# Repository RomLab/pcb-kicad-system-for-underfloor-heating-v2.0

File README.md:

# PCB for underfloor heating system v2.0

There are here schematics, PCBs, 3D views and Gerber data for devices in underfloor heating system. There are two types folders with version KiCAD 5 and KiCAD 7. The libraries are [here](https://github.com/RomLab/kicad-library).

More information at https://github.com/RomLab/system-for-underfloor-heating-v2.0

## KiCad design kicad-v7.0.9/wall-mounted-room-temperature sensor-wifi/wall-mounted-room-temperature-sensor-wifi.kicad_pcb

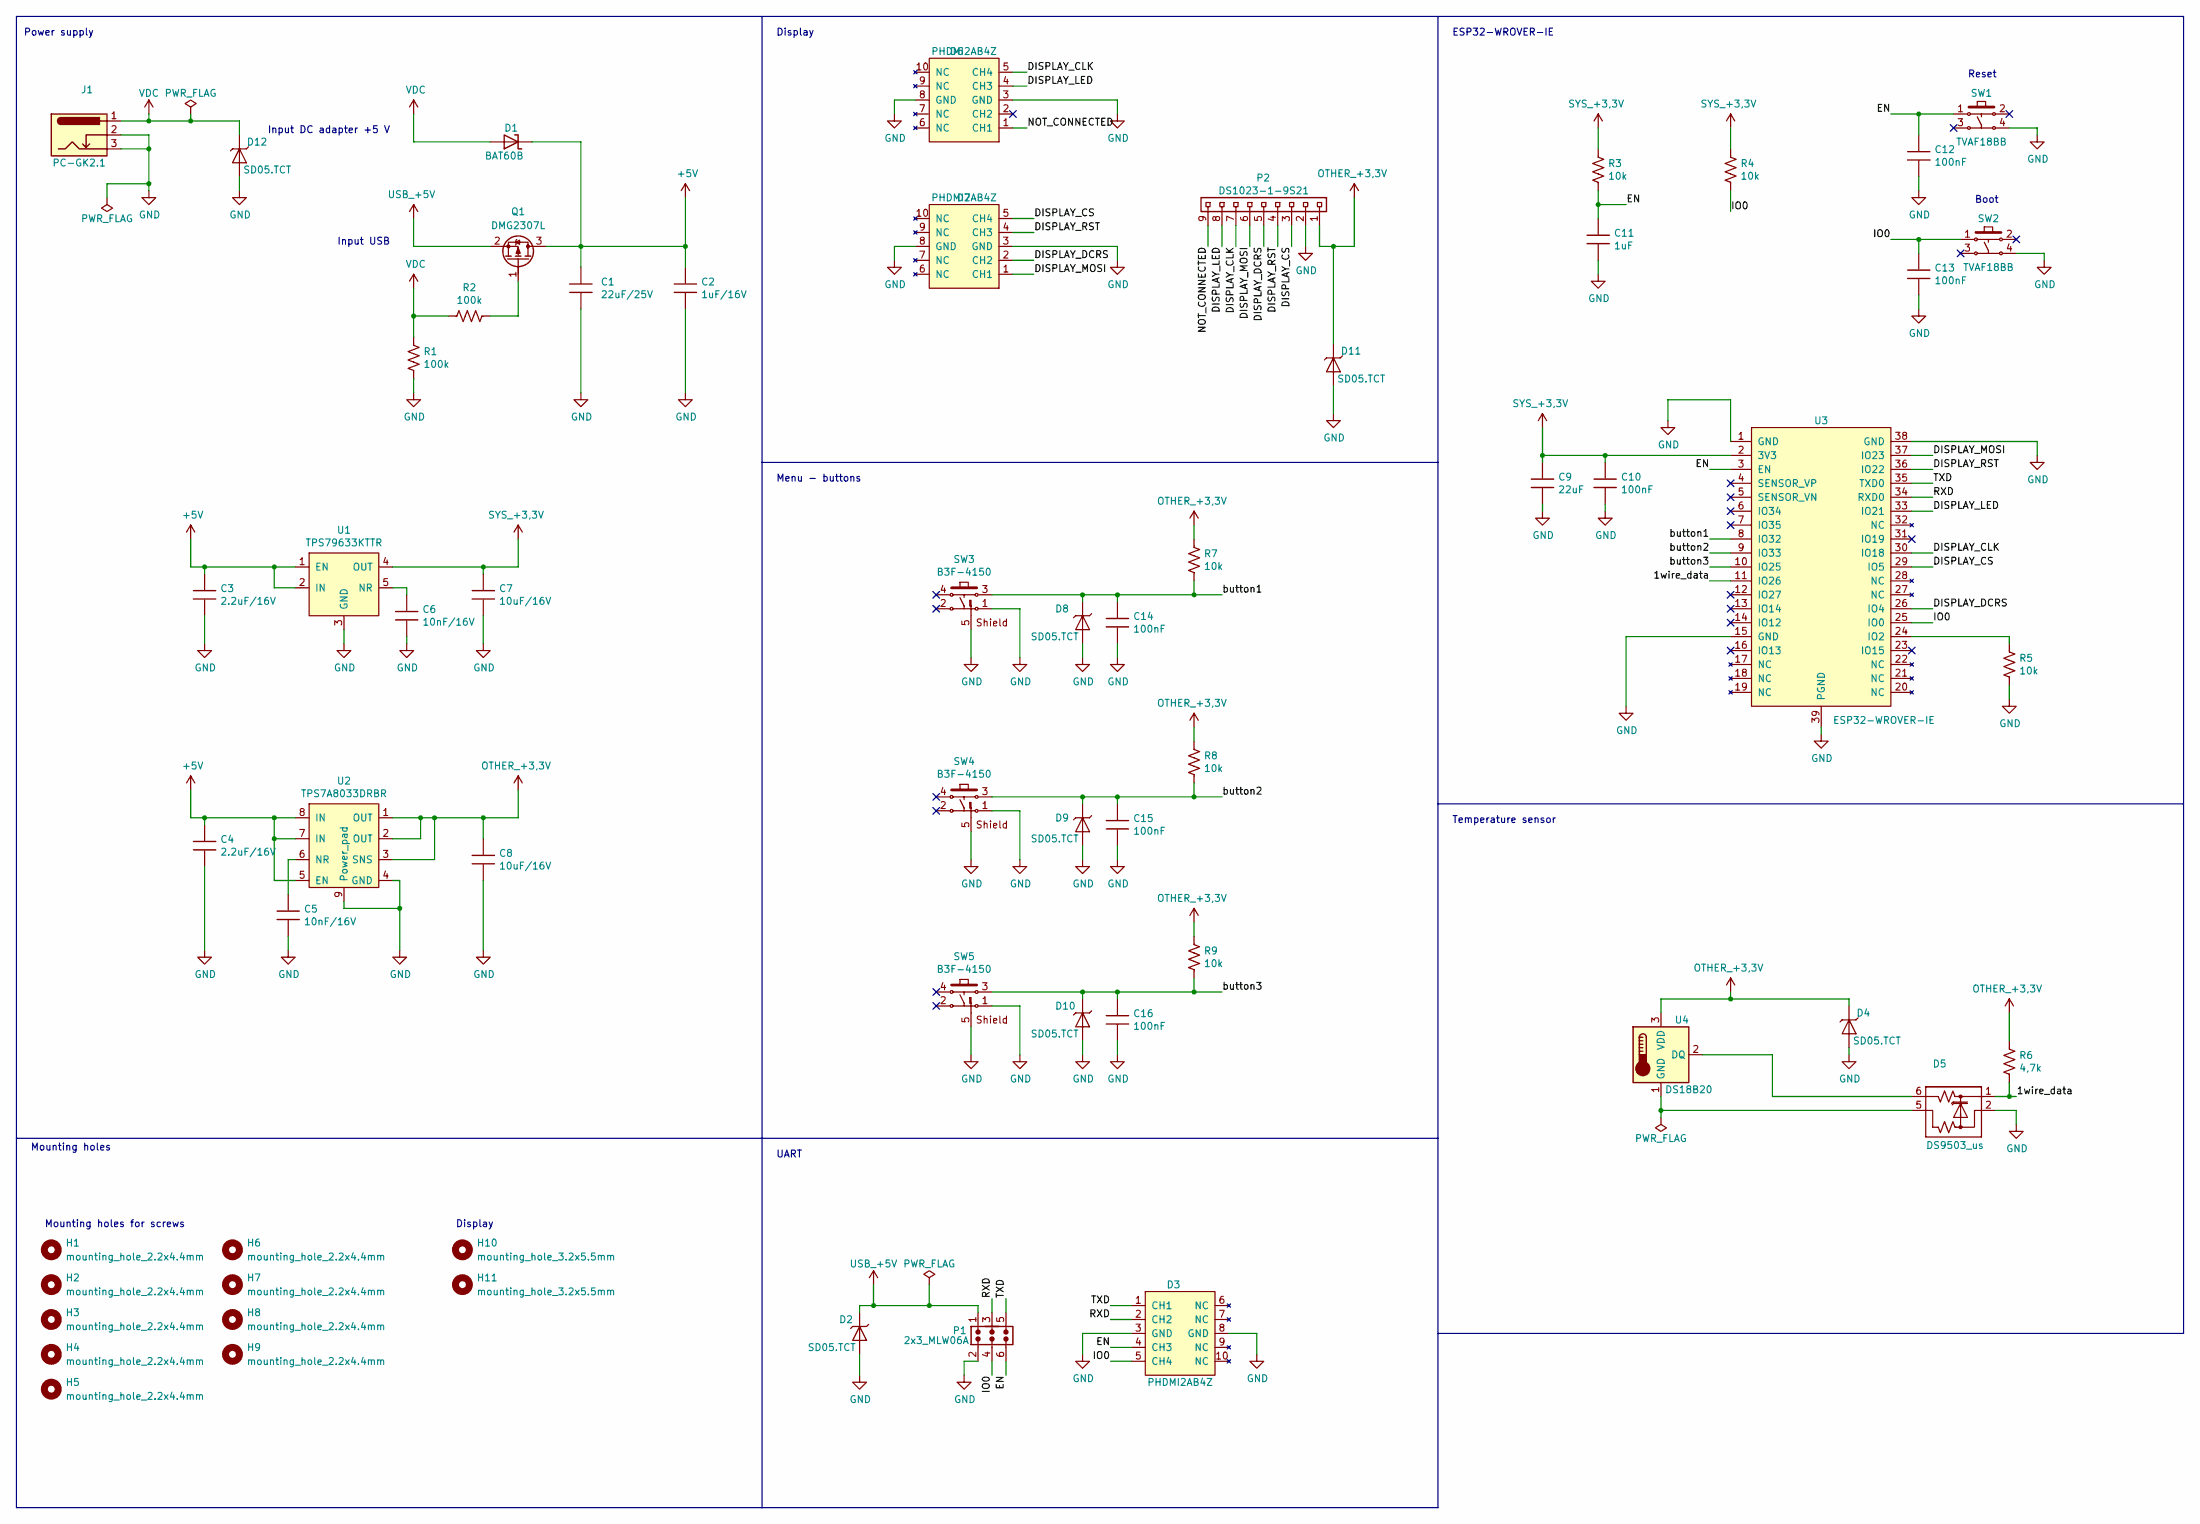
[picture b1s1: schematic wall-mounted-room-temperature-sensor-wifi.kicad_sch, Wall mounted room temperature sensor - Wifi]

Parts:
C1: 22uF/25V; c_0805
C2: 1uF/16V; c_0805
C3, C4: 2.2uF/16V; c_0805
C5, C6: 10nF/16V; c_0805
C7, C8: 10uF/16V; c_0805
C9: 22uF; c_0805
C10, C12, C13, C14, C15, C16: 100nF; c_0805
C11: 1uF; c_0805
D1: BAT60B; sod_323
D2, D4, D8, D9, D10, D11, D12: SD05.TCT; sod_323
D3, D6, D7: PHDMI2AB4Z; dfn_2510a_10
D5: DS9503_us; tsoc_6
H1, H2, H3, H4, H5, H6, H7, H8, H9: mounting_hole_2.2x4.4mm
H10, H11: mounting_hole_3.2x5.5mm
J1: PC-GK2.1
P1: 2x3_MLW06A
P2: DS1023-1-9S21; 1x9_pin_socket_2.54mm_vertical_8.5mm
Q1: DMG2307L; sot_23_3
R1, R2: 100k; r_0805
R3, R4, R5, R7, R8, R9: 10k; r_0805
R6: 4,7k; r_0805
SW1, SW2: TVAF18BB
SW3, SW4, SW5: B3F-4150
U1: TPS79633KTTR; to_263_5
U2: TPS7A8033DRBR; son_8
U3: ESP32-WROVER-IE
U4: DS18B20; to_92_in_line

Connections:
+5V: C1.1, C2.1, C3.1, C4.1, D1.1 (K), Q1.3 (D), U1.1 (EN), U1.2 (IN), U2.5 (EN), U2.7 (IN), U2.8 (IN)
/1wire_data: D5.1 (K), R6.2, U3.11 (IO26)
/DISPLAY_CLK: D6.5 (CH4), P2.7, U3.30 (IO18)
/DISPLAY_CS: D7.5 (CH4), P2.3, U3.29 (IO5)
/DISPLAY_DCRS: D7.2 (CH2), P2.5, U3.26 (IO4)
/DISPLAY_LED: D6.4 (CH3), P2.8, U3.33 (IO21)
/DISPLAY_MOSI: D7.1 (CH1), P2.6, U3.37 (IO23)
/DISPLAY_RST: D7.4 (CH3), P2.4, U3.36 (IO22)
/EN: C11.1, C12.1, D3.4 (CH3), P1.6, R3.2, SW1.1, U3.3 (EN)
/IO0: C13.1, D3.5 (CH4), P1.4, R4.2, SW2.1, U3.25 (IO0)
/NOT_CONNECTED: D6.1 (CH1), P2.9
/RXD: D3.2 (CH2), P1.3, U3.34 (RXD0)
/TXD: D3.1 (CH1), P1.5, U3.35 (TXD0)
/button1: C14.1, D8.1 (K), R7.2, SW3.3, U3.8 (IO32)
/button2: C15.1, D9.1 (K), R8.2, SW4.3, U3.9 (IO33)
/button3: C16.1, D10.1 (K), R9.2, SW5.3, U3.10 (IO25)
GND: C1.2, C2.2, C3.2, C4.2, C5.2, C6.2, C7.2, C8.2, C9.2, C10.2, C11.2, C12.2, C13.2, C14.2, C15.2, C16.2, D2.2 (A), D3.3 (GND), D3.8 (GND), D4.2 (A), D5.2 (A), D6.3 (GND), D6.8 (GND), D7.3 (GND), D7.8 (GND), D8.2 (A), D9.2 (A), D10.2 (A), D11.2 (A), D12.2 (A), J1.2, J1.3, P1.2, P2.2, R1.2, R5.2, SW1.4, SW2.4, SW3.1, SW3.5 (GND), SW4.1, SW4.5 (GND), SW5.1, SW5.5 (GND), U1.3 (GND), U2.4 (GND), U2.9 (Power_pad), U3.1 (GND), U3.15 (GND), U3.38 (GND), U3.39 (PGND)
unnamed: Q1.1 (G), R2.2
unnamed: C6.1, U1.5 (NR)
unnamed: C5.1, U2.6 (NR)
unnamed: R5.1, U3.24 (IO2)
unnamed: D5.6 (K), U4.2 (DQ)
unnamed: D5.5 (A), U4.1 (GND)
OTHER_+3,3V: C8.1, D4.1 (K), D11.1 (K), P2.1, R6.1, R7.1, R8.1, R9.1, U2.1 (OUT), U2.2 (OUT), U2.3 (SNS), U4.3 (VDD)
SYS_+3,3V: C7.1, C9.1, C10.1, R3.1, R4.1, U1.4 (OUT), U3.2 (3V3)
USB_+5V: D2.1 (K), P1.1, Q1.2 (S)
VDC: D1.2 (A), D12.1 (K), J1.1, R1.1, R2.1

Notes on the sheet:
Mounting holes
Reset
Input DC adapter +5 V
Display
Boot
Menu - buttons
Power supply
Temperature sensor
Mounting holes for screws
Input USB
UART
ESP32-WROVER-IE

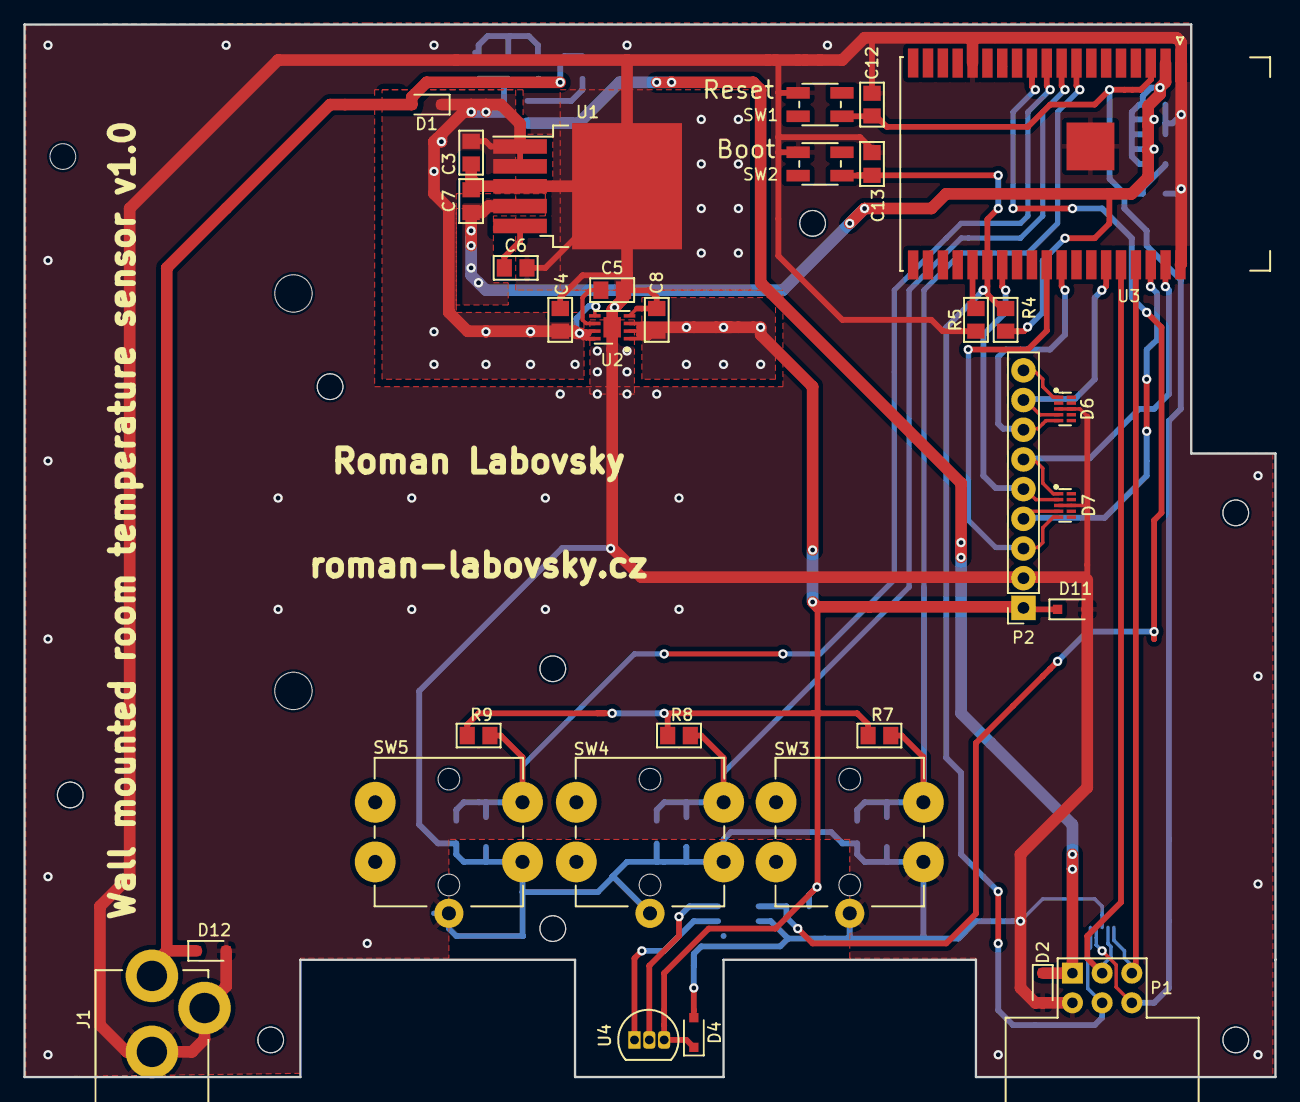
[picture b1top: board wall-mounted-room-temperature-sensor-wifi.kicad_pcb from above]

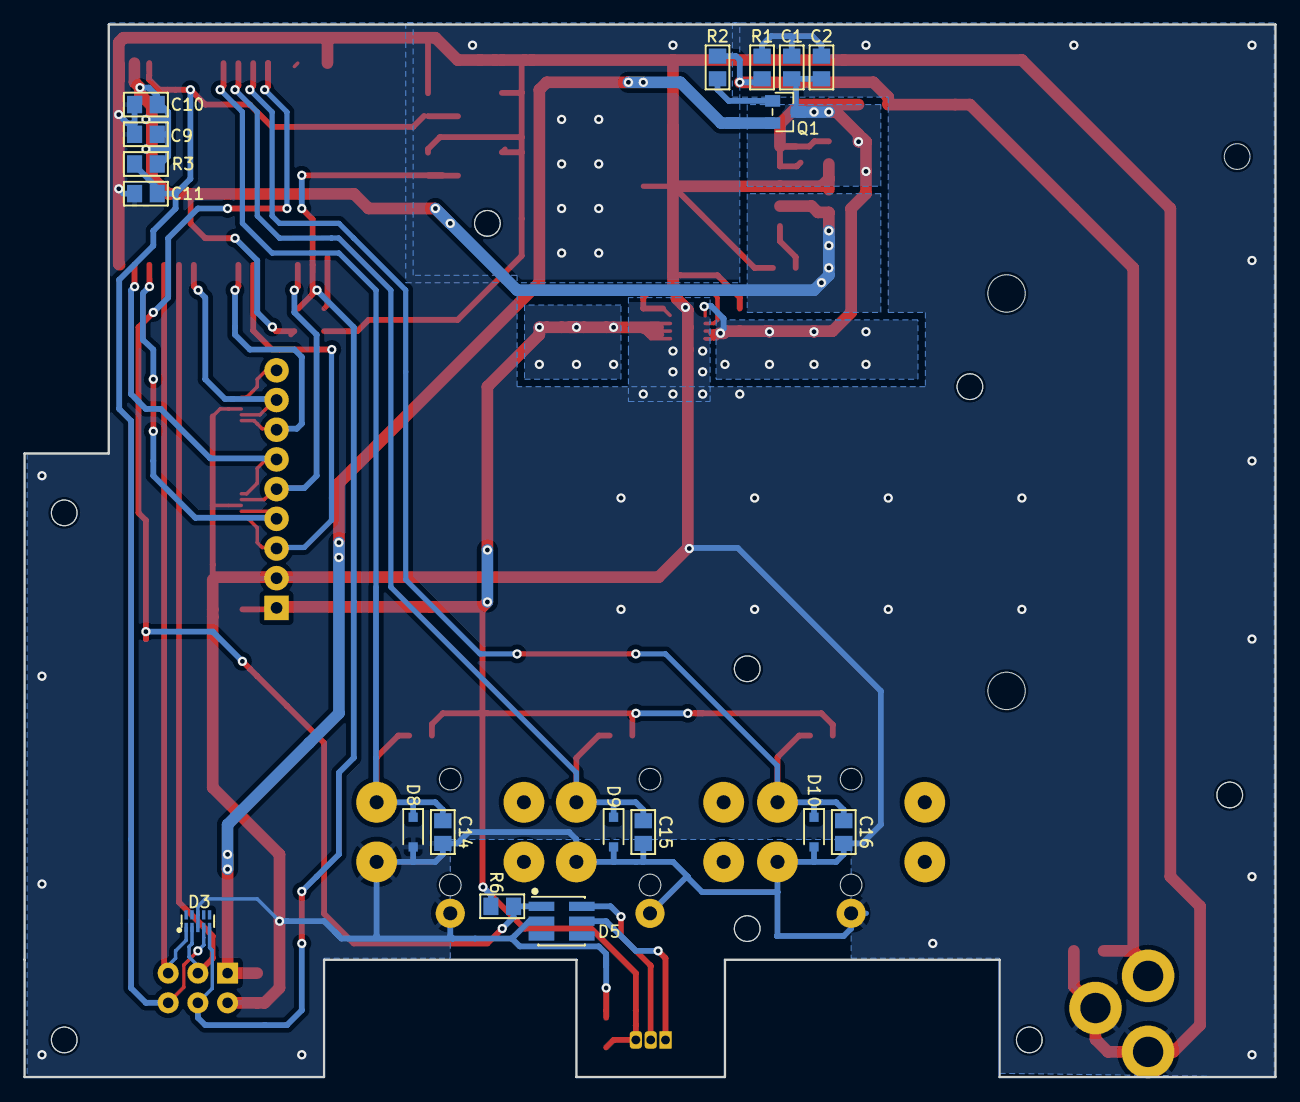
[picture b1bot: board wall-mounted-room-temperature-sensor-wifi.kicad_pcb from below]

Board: 2 copper layers, 107.0 x 90.0 mm, 61 parts (18 on the bottom side), 27 nets.

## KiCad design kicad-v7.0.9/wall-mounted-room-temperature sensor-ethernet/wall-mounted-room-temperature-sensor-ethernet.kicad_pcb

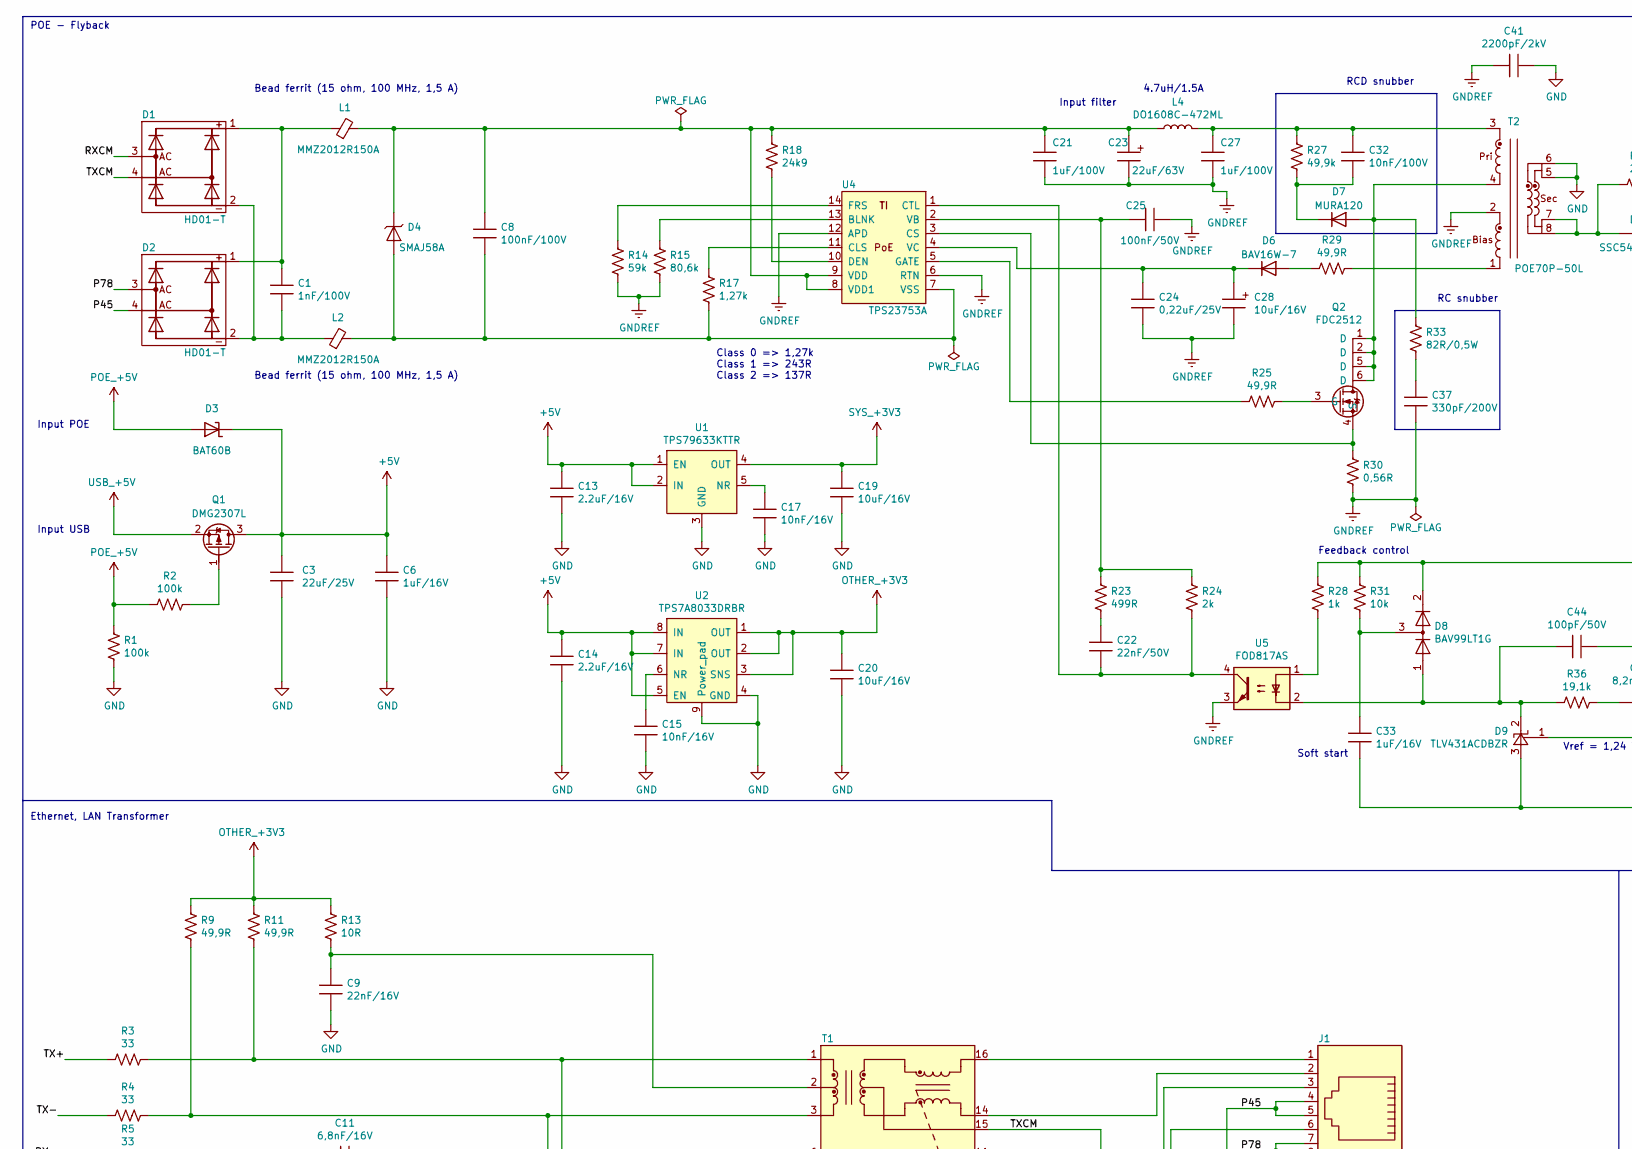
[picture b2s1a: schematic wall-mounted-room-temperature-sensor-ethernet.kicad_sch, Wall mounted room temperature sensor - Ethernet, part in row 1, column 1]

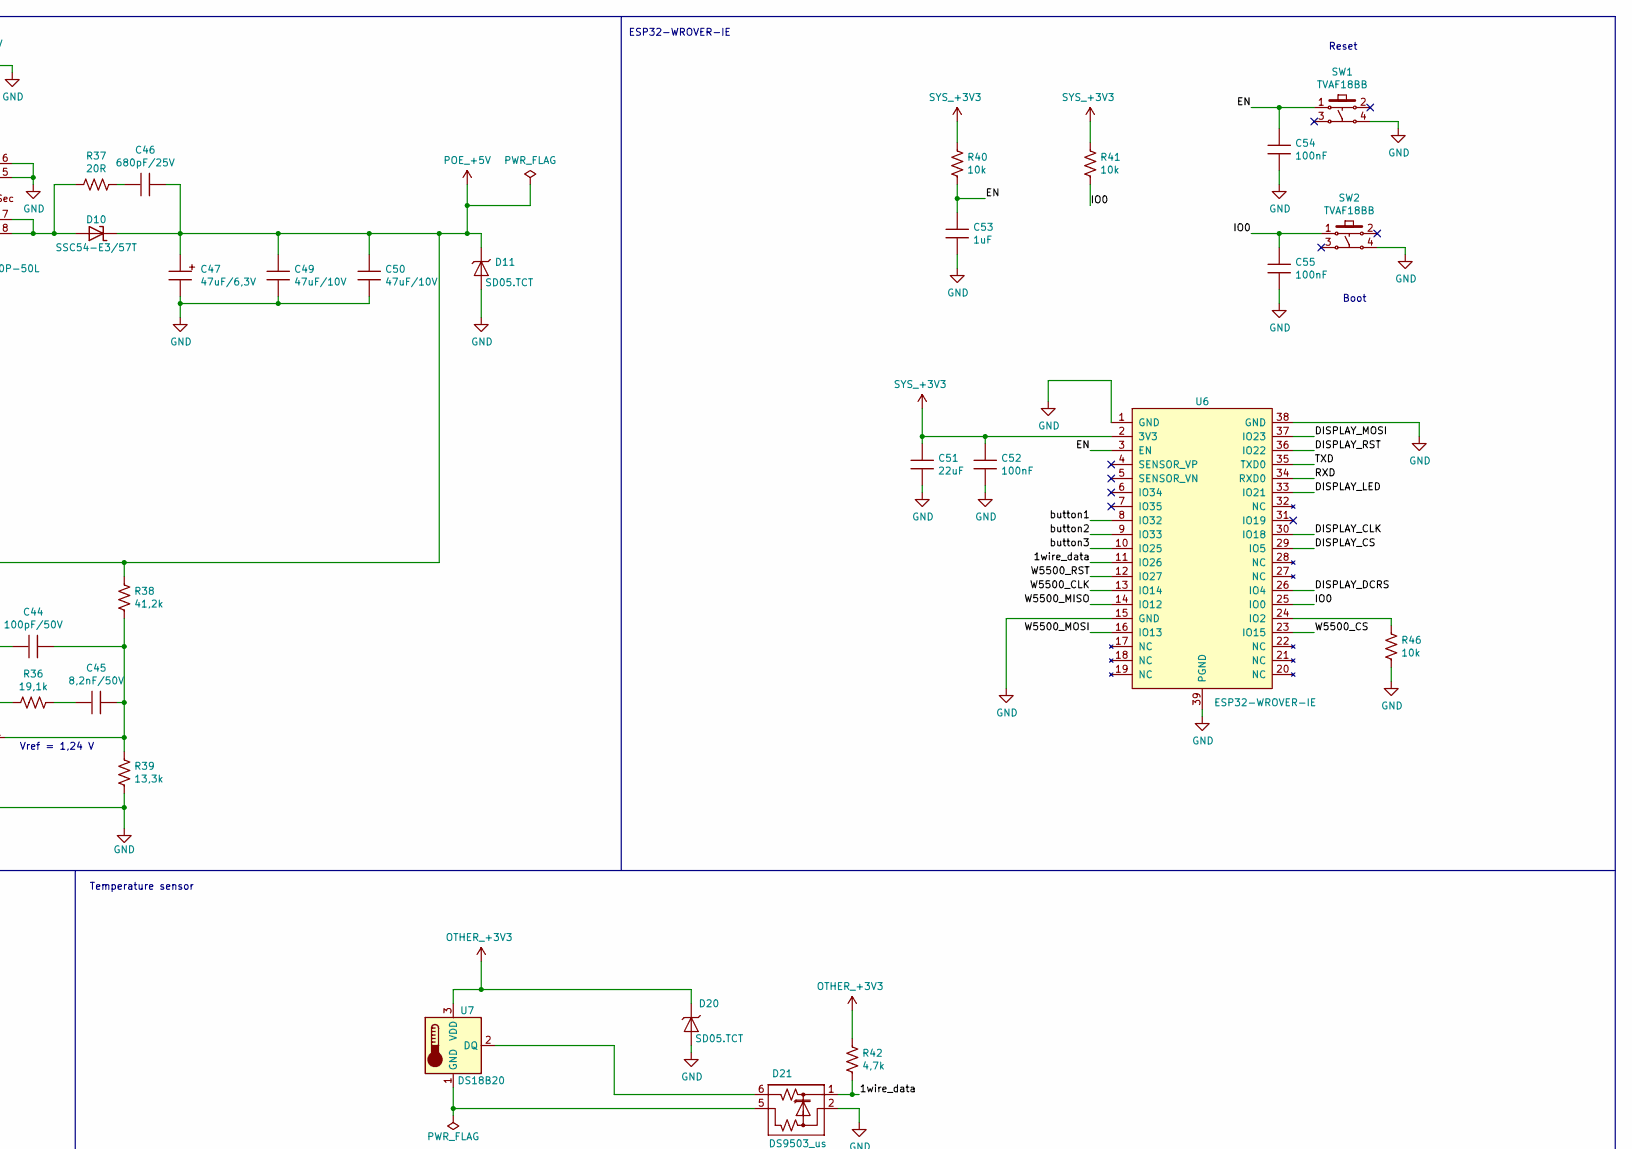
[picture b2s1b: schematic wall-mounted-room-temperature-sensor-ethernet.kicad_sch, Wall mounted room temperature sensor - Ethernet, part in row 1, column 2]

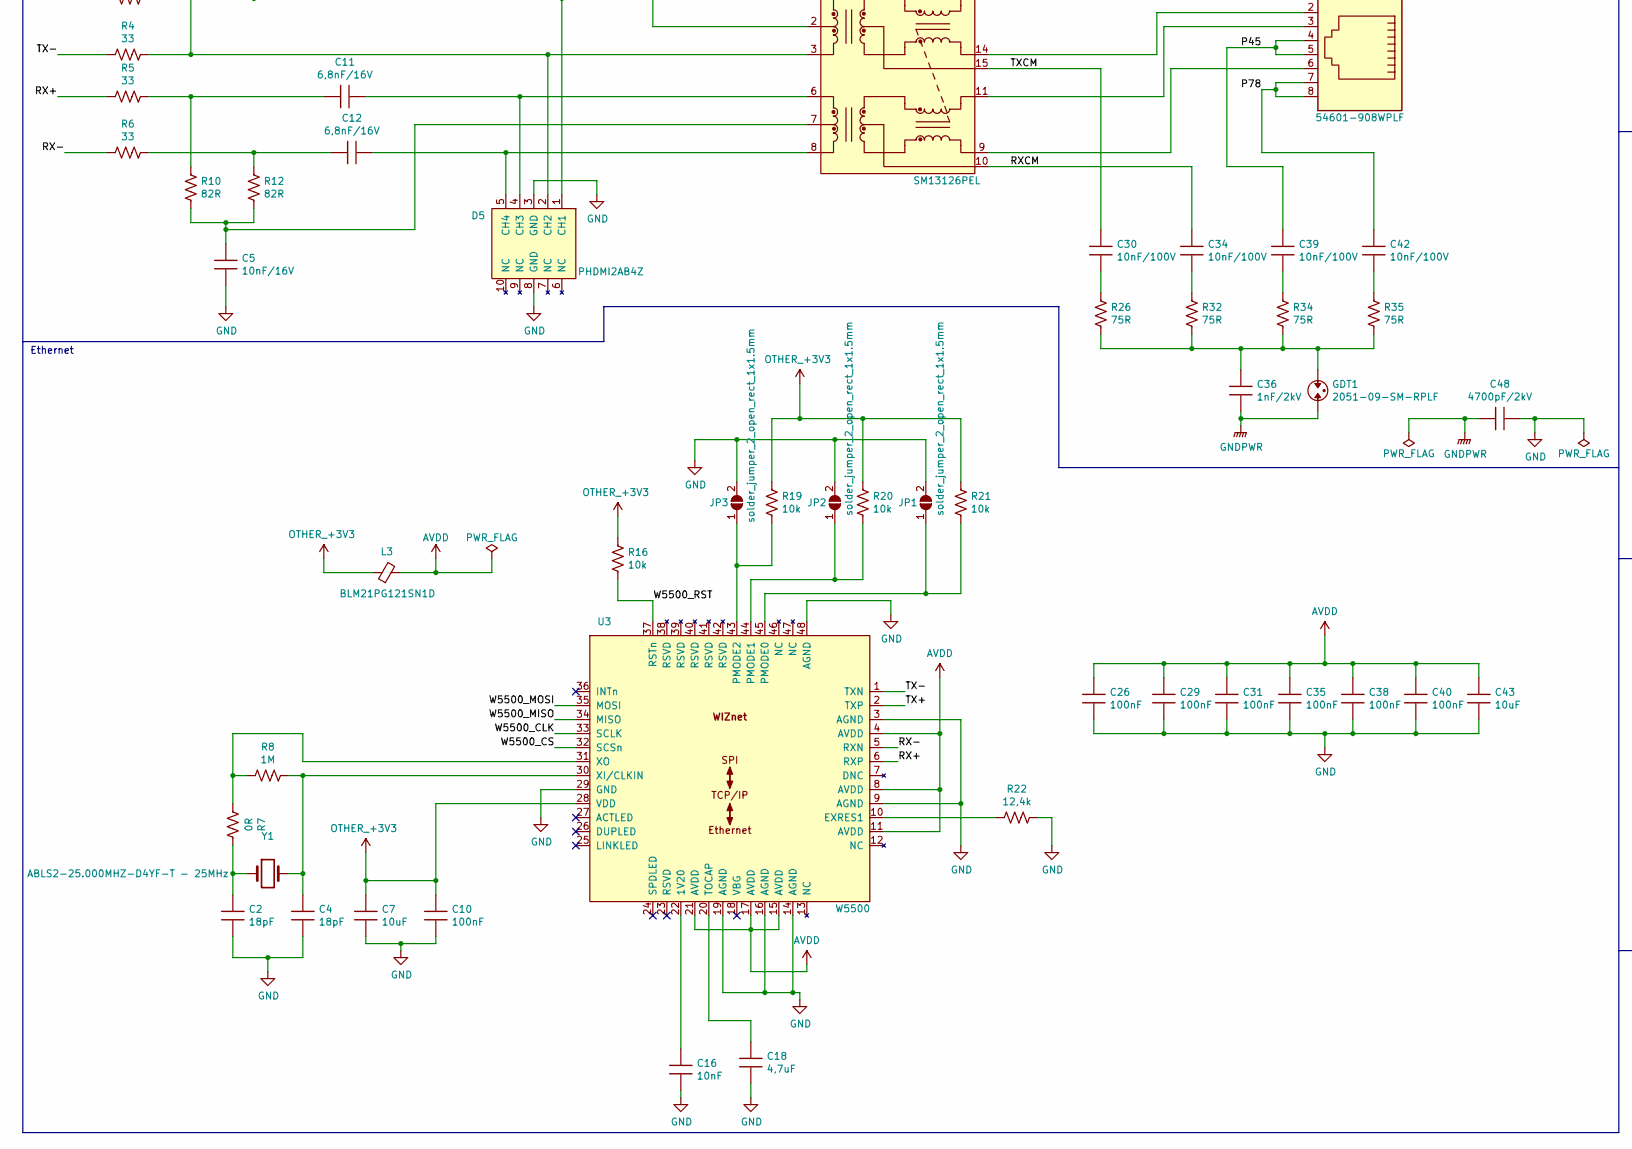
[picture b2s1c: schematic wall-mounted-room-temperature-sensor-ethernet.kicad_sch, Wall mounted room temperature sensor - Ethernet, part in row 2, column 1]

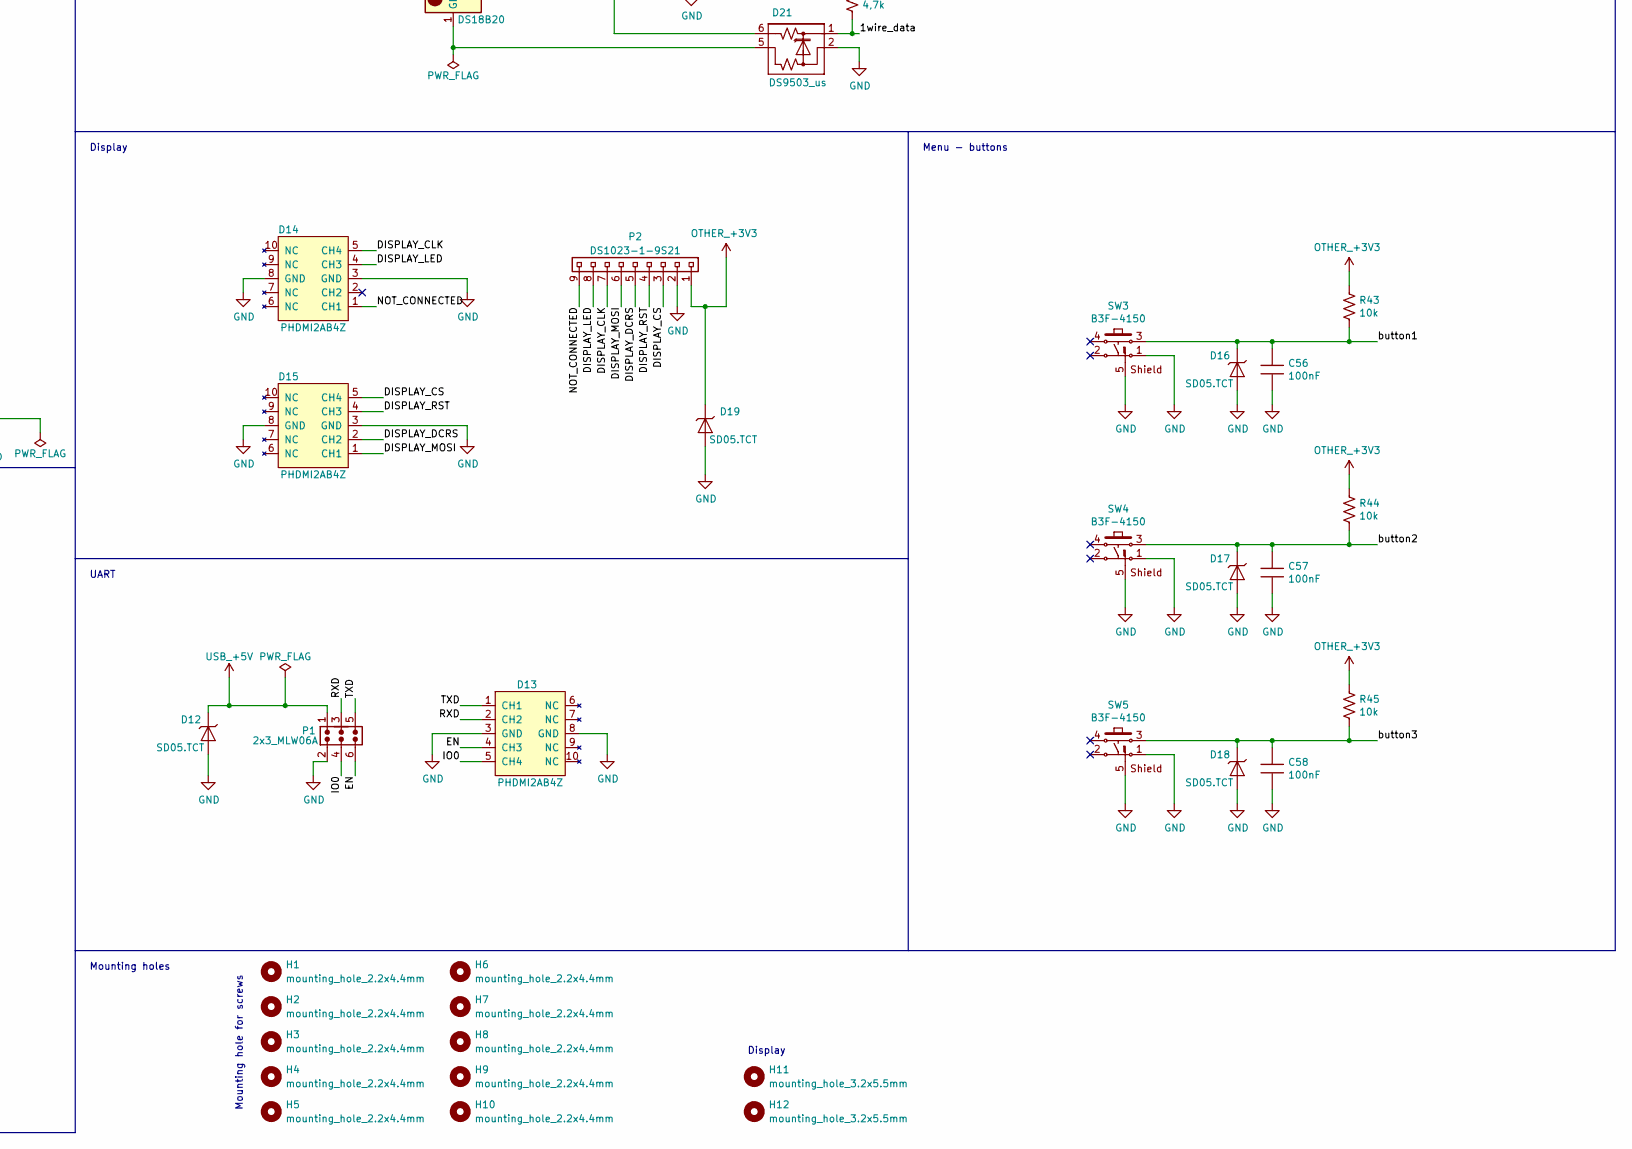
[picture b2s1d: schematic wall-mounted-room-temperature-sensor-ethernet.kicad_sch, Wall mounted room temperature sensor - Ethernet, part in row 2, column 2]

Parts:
C1: 1nF/100V; c_0805
C2, C4: 18pF; c_0805
C3: 22uF/25V; c_0805
C5, C15, C17: 10nF/16V; c_0805
C6, C33: 1uF/16V; c_0805
C7, C43: 10uF; c_0805
C8: 100nF/100V; c_0805
C9: 22nF/16V; c_0805
C10, C26, C29, C31, C35, C38, C40, C52, C54, C55, C56, C57, C58: 100nF; c_0805
C11, C12: 6,8nF/16V; c_0805
C13, C14: 2.2uF/16V; c_0805
C16: 10nF; c_0805
C18: 4,7uF; c_0805
C19, C20: 10uF/16V; c_0805
C21, C27: 1uF/100V; c_1206
C22: 22nF/50V; c_0805
C23: 22uF/63V; c_elec_6.3x7.7
C24: 0,22uF/25V; c_0805
C25: 100nF/50V; c_0805
C28: 10uF/16V; c_elec_4x5.8
C30, C32, C34, C39, C42: 10nF/100V; c_0805
C36: 1nF/2kV; c_1206
C37: 330pF/200V; c_0805
C41: 2200pF/2kV; c_1812
C44: 100pF/50V; c_0805
C45: 8,2nF/50V; c_0805
C46: 680pF/25V; c_0805
C47: 47uF/6,3V; c_elec_4x5.8
C48: 4700pF/2kV; c_1812
C49, C50: 47uF/10V; c_0805
C51: 22uF; c_0805
C53: 1uF; c_0805
D1, D2: HD01-T; mini_dip
D3: BAT60B; sod_323
D4: SMAJ58A; do_214ac
D5, D13, D14, D15: PHDMI2AB4Z; dfn_2510a_10
D6: BAV16W-7; sod_123
D7: MURA120; sma
D8: BAV99LT1G; sot_23_3
D9: TLV431ACDBZR; sot_23_3
D10: SSC54-E3/57T; smc_do_214ab
D11, D12, D16, D17, D18, D19, D20: SD05.TCT; sod_323
D21: DS9503_us; tsoc_6
GDT1: 2051-09-SM-RPLF
H1, H2, H3, H4, H5, H6, H7, H8, H9, H10: mounting_hole_2.2x4.4mm
H11, H12: mounting_hole_3.2x5.5mm
J1: 54601-908WPLF
JP1, JP2, JP3: solder_jumper_2_open_rect_1x1.5mm
L1, L2: MMZ2012R150A; ferrite_bead_0805
L3: BLM21PG121SN1D; ferrite_bead_0805
L4: DO1608C-472ML
P1: 2x3_MLW06A
P2: DS1023-1-9S21; 1x9_pin_socket_2.54mm_vertical_8.5mm
Q1: DMG2307L; sot_23_3
Q2: FDC2512; tsot_23_6
R1, R2: 100k; r_0805
R3, R4, R5, R6: 33; r_0805
R7: 0R; r_0805
R8: 1M; r_0805
R9, R11, R25, R29: 49,9R; r_0805
R10, R12: 82R; r_1206
R13: 10R; r_0805
R14: 59k; r_0805
R15: 80,6k; r_0805
R16, R19, R20, R21, R31, R40, R41, R43, R44, R45, R46: 10k; r_0805
R17: 1,27k; r_0805
R18: 24k9; r_0805
R22: 12,4k; r_0805
R23: 499R; r_0805
R24: 2k; r_0805
R26, R32, R34, R35: 75R; r_0805
R27: 49,9k; r_0805
R28: 1k; r_0805
R30: 0,56R; r_1206
R33: 82R/0,5W; r_1206
R36: 19,1k; r_0805
R37: 20R; r_0805
R38: 41,2k; r_0805
R39: 13,3k; r_0805
R42: 4,7k; r_0805
SW1, SW2: TVAF18BB
SW3, SW4, SW5: B3F-4150
T1: SM13126PEL
T2: POE70P-50L
U1: TPS79633KTTR; to_263_5
U2: TPS7A8033DRBR; son_8
U3: W5500; lqfp_48
U4: TPS23753A; tssop_14
U5: FOD817AS; dip_4
U6: ESP32-WROVER-IE
U7: DS18B20; to_92_in_line
Y1: ABLS2-25.000MHZ-D4YF-T - 25MHz; ABLS2-25.000MHZ-D4YF-T

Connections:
+5V: C3.1, C6.1, C13.1, C14.1, D3.1 (K), Q1.3 (D), U1.1 (EN), U1.2 (IN), U2.5 (EN), U2.7 (IN), U2.8 (IN)
/1wire_data: D21.1 (K), R42.2, U6.11 (IO26)
/DISPLAY_CLK: D14.5 (CH4), P2.7, U6.30 (IO18)
/DISPLAY_CS: D15.5 (CH4), P2.3, U6.29 (IO5)
/DISPLAY_DCRS: D15.2 (CH2), P2.5, U6.26 (IO4)
/DISPLAY_LED: D14.4 (CH3), P2.8, U6.33 (IO21)
/DISPLAY_MOSI: D15.1 (CH1), P2.6, U6.37 (IO23)
/DISPLAY_RST: D15.4 (CH3), P2.4, U6.36 (IO22)
/EN: C53.1, C54.1, D13.4 (CH3), P1.6, R40.2, SW1.1, U6.3 (EN)
/IO0: C55.1, D13.5 (CH4), P1.4, R41.2, SW2.1, U6.25 (IO0)
/NOT_CONNECTED: D14.1 (CH1), P2.9
/P45: C39.1, D2.4, J1.4, J1.5
/P78: C42.1, D2.3, J1.7, J1.8
/RX+: R5.1, U3.6 (RXP)
/RX-: R6.1, U3.5 (RXN)
/RXCM: C34.1, D1.3, T1.10
/RXD: D13.2 (CH2), P1.3, U6.34 (RXD0)
/TX+: R3.1, U3.2 (TXP)
/TX-: R4.1, U3.1 (TXN)
/TXCM: C30.1, D1.4, T1.15
/TXD: D13.1 (CH1), P1.5, U6.35 (TXD0)
/W5500_CLK: U3.33 (SCLK), U6.13 (IO14)
/W5500_CS: U3.32 (SCSn), U6.23 (IO15)
/W5500_MISO: U3.34 (MISO), U6.14 (IO12)
/W5500_MOSI: U3.35 (MOSI), U6.16 (IO13)
/W5500_RST: R16.2, U3.37 (RSTn), U6.12 (IO27)
/button1: C56.1, D16.1 (K), R43.2, SW3.3, U6.8 (IO32)
/button2: C57.1, D17.1 (K), R44.2, SW4.3, U6.9 (IO33)
/button3: C58.1, D18.1 (K), R45.2, SW5.3, U6.10 (IO25)
AVDD: C26.1, C29.1, C31.1, C35.1, C38.1, C40.1, C43.1, L3.2, U3.4 (AVDD), U3.8 (AVDD), U3.11 (AVDD), U3.15 (AVDD), U3.17 (AVDD), U3.21 (AVDD)
GND: C2.2, C3.2, C4.2, C5.2, C6.2, C7.2, C9.2, C10.2, C13.2, C14.2, C15.2, C16.2, C17.2, C18.2, C19.2, C20.2, C26.2, C29.2, C31.2, C33.2, C35.2, C38.2, C40.2, C41.2, C43.2, C47.2, C48.2, C49.1, C50.2, C51.2, C52.2, C53.2, C54.2, C55.2, C56.2, C57.2, C58.2, D5.3 (GND), D5.8 (GND), D9.3 (A), D11.2 (A), D12.2 (A), D13.3 (GND), D13.8 (GND), D14.3 (GND), D14.8 (GND), D15.3 (GND), D15.8 (GND), D16.2 (A), D17.2 (A), D18.2 (A), D19.2 (A), D20.2 (A), D21.2 (A), JP1.2 (B), JP2.2 (B), JP3.2 (B), P1.2, P2.2, R1.2, R22.2, R39.2, R46.2, SW1.4, SW2.4, SW3.1, SW3.5 (GND), SW4.1, SW4.5 (GND), SW5.1, SW5.5 (GND), T2.5, T2.6, U1.3 (GND), U2.4 (GND), U2.9 (Power_pad), U3.3 (AGND), U3.9 (AGND), U3.14 (AGND), U3.16 (AGND), U3.19 (AGND), U3.29 (GND), U3.48 (AGND), U6.1 (GND), U6.15 (GND), U6.38 (GND), U6.39 (PGND)
GNDPWR: C36.2, C48.1, GDT1.2
GNDREF: C21.2, C23.2, C24.2, C25.2, C27.2, C28.2, C37.2, C41.1, R14.2, R15.2, R30.2, T2.2, U4.6 (RTN), U4.12 (APD), U5.3
unnamed: C1.1, D1.1, D2.1, L1.1
unnamed: C1.2, D1.2, D2.2, L2.1
unnamed: C2.1, R7.2, Y1.1
unnamed: C5.1, R10.2, R12.2, T1.7
unnamed: C9.1, R13.2, T1.2
unnamed: C11.1, R5.2, R10.1
unnamed: C12.1, R6.2, R12.1
unnamed: C22.1, R23.2
unnamed: C27.1, C32.1, L4.2, R27.1, T2.3
unnamed: C30.2, R26.1
unnamed: C33.1, D8.3 (K), R31.2
unnamed: C34.2, R32.1
unnamed: C36.1, GDT1.1, R26.2, R32.2, R34.2, R35.2
unnamed: C37.1, R33.2
unnamed: C39.2, R34.1
unnamed: C42.2, R35.1
unnamed: C45.1, R36.2
unnamed: C46.1, R37.2
unnamed: C8.2, D4.2 (A), L2.2, R17.2, U4.7 (VSS)
unnamed: C8.1, C21.1, C23.1, D4.1 (K), L1.2, L4.1, R18.1, U4.8 (VDD1), U4.9 (VDD)
unnamed: D5.1 (CH1), R3.2, R11.2, T1.1
unnamed: D5.2 (CH2), R4.2, R9.2, T1.3
unnamed: C11.2, D5.4 (CH3), T1.6
unnamed: C12.2, D5.5 (CH4), T1.8
unnamed: D6.2 (A), R29.1
unnamed: C24.1, C28.1, D6.1 (K), U4.4 (VC)
unnamed: D7.2 (A), Q2.1 (D), Q2.2 (D), Q2.5 (D), Q2.6 (D), R33.1, T2.4
unnamed: C32.2, D7.1 (K), R27.2
unnamed: C44.2, C45.2, D9.1 (FB), R38.2, R39.1
unnamed: C44.1, D8.1 (K), D9.2 (K), R36.1, U5.2
unnamed: D10.2 (A), R37.1, T2.7, T2.8
unnamed: J1.1, T1.16
unnamed: J1.2, T1.14
unnamed: J1.3, T1.11
unnamed: J1.6, T1.9
unnamed: JP1.1 (A), R21.2, U3.45 (PMODE0)
unnamed: JP2.1 (A), R20.2, U3.44 (PMODE1)
unnamed: JP3.1 (A), R19.2, U3.43 (PMODE2)
unnamed: Q1.1 (G), R2.2
unnamed: Q2.3 (G), R25.2
unnamed: Q2.4 (S), R30.1, U4.3 (CS)
unnamed: R28.2, U5.1
unnamed: R29.2, T2.1
unnamed: C17.1, U1.5 (NR)
unnamed: C15.1, U2.6 (NR)
unnamed: C16.1, U3.22 (1V20)
unnamed: R22.1, U3.10 (EXRES1)
unnamed: C18.1, U3.20 (TOCAP)
unnamed: C4.1, R8.2, U3.30 (XI/CLKIN), Y1.2
unnamed: R7.1, R8.1, U3.31 (XO)
unnamed: R15.1, U4.13 (BLNK)
unnamed: R17.1, U4.11 (CLS)
unnamed: C22.2, R24.2, U4.1 (CTL), U5.4
unnamed: R18.2, U4.10 (DEN)
unnamed: R14.1, U4.14 (FRS)
unnamed: R25.1, U4.5 (GATE)
unnamed: C25.1, R23.1, R24.1, U4.2 (VB)
unnamed: R46.1, U6.24 (IO2)
unnamed: D21.6 (K), U7.2 (DQ)
unnamed: D21.5 (A), U7.1 (GND)
OTHER_+3V3: C7.1, C10.1, C20.1, D19.1 (K), D20.1 (K), L3.1, P2.1, R9.1, R11.1, R13.1, R16.1, R19.1, R20.1, R21.1, R42.1, R43.1, R44.1, R45.1, U2.1 (OUT), U2.2 (OUT), U2.3 (SNS), U3.28 (VDD), U7.3 (VDD)
POE_+5V: C46.2, C47.1, C49.2, C50.1, D3.2 (A), D8.2 (A), D10.1 (K), D11.1 (K), R1.1, R2.1, R28.1, R31.1, R38.1
SYS_+3V3: C19.1, C51.1, C52.1, R40.1, R41.1, U1.4 (OUT), U6.2 (3V3)
USB_+5V: D12.1 (K), P1.1, Q1.2 (S)

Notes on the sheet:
Class 0 => 1,27k Class 1 => 243R Class 2 => 137R
Bead ferrit (15 ohm, 100 MHz, 1,5 A)
POE - Flyback
4.7uH/1.5A
Feedback control
Display
RC snubber
Soft start
Menu - buttons
Mounting holes
UART
Mounting hole for screws
ESP32-WROVER-IE
Boot
Ethernet, LAN Transformer
Vref = 1,24 V
RCD snubber
Input POE
Temperature sensor
Reset
Ethernet
Input USB
Input filter
